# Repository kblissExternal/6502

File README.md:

# 6502
My implementation of Ben Eater's 6502 design (https://eater.net/6502).

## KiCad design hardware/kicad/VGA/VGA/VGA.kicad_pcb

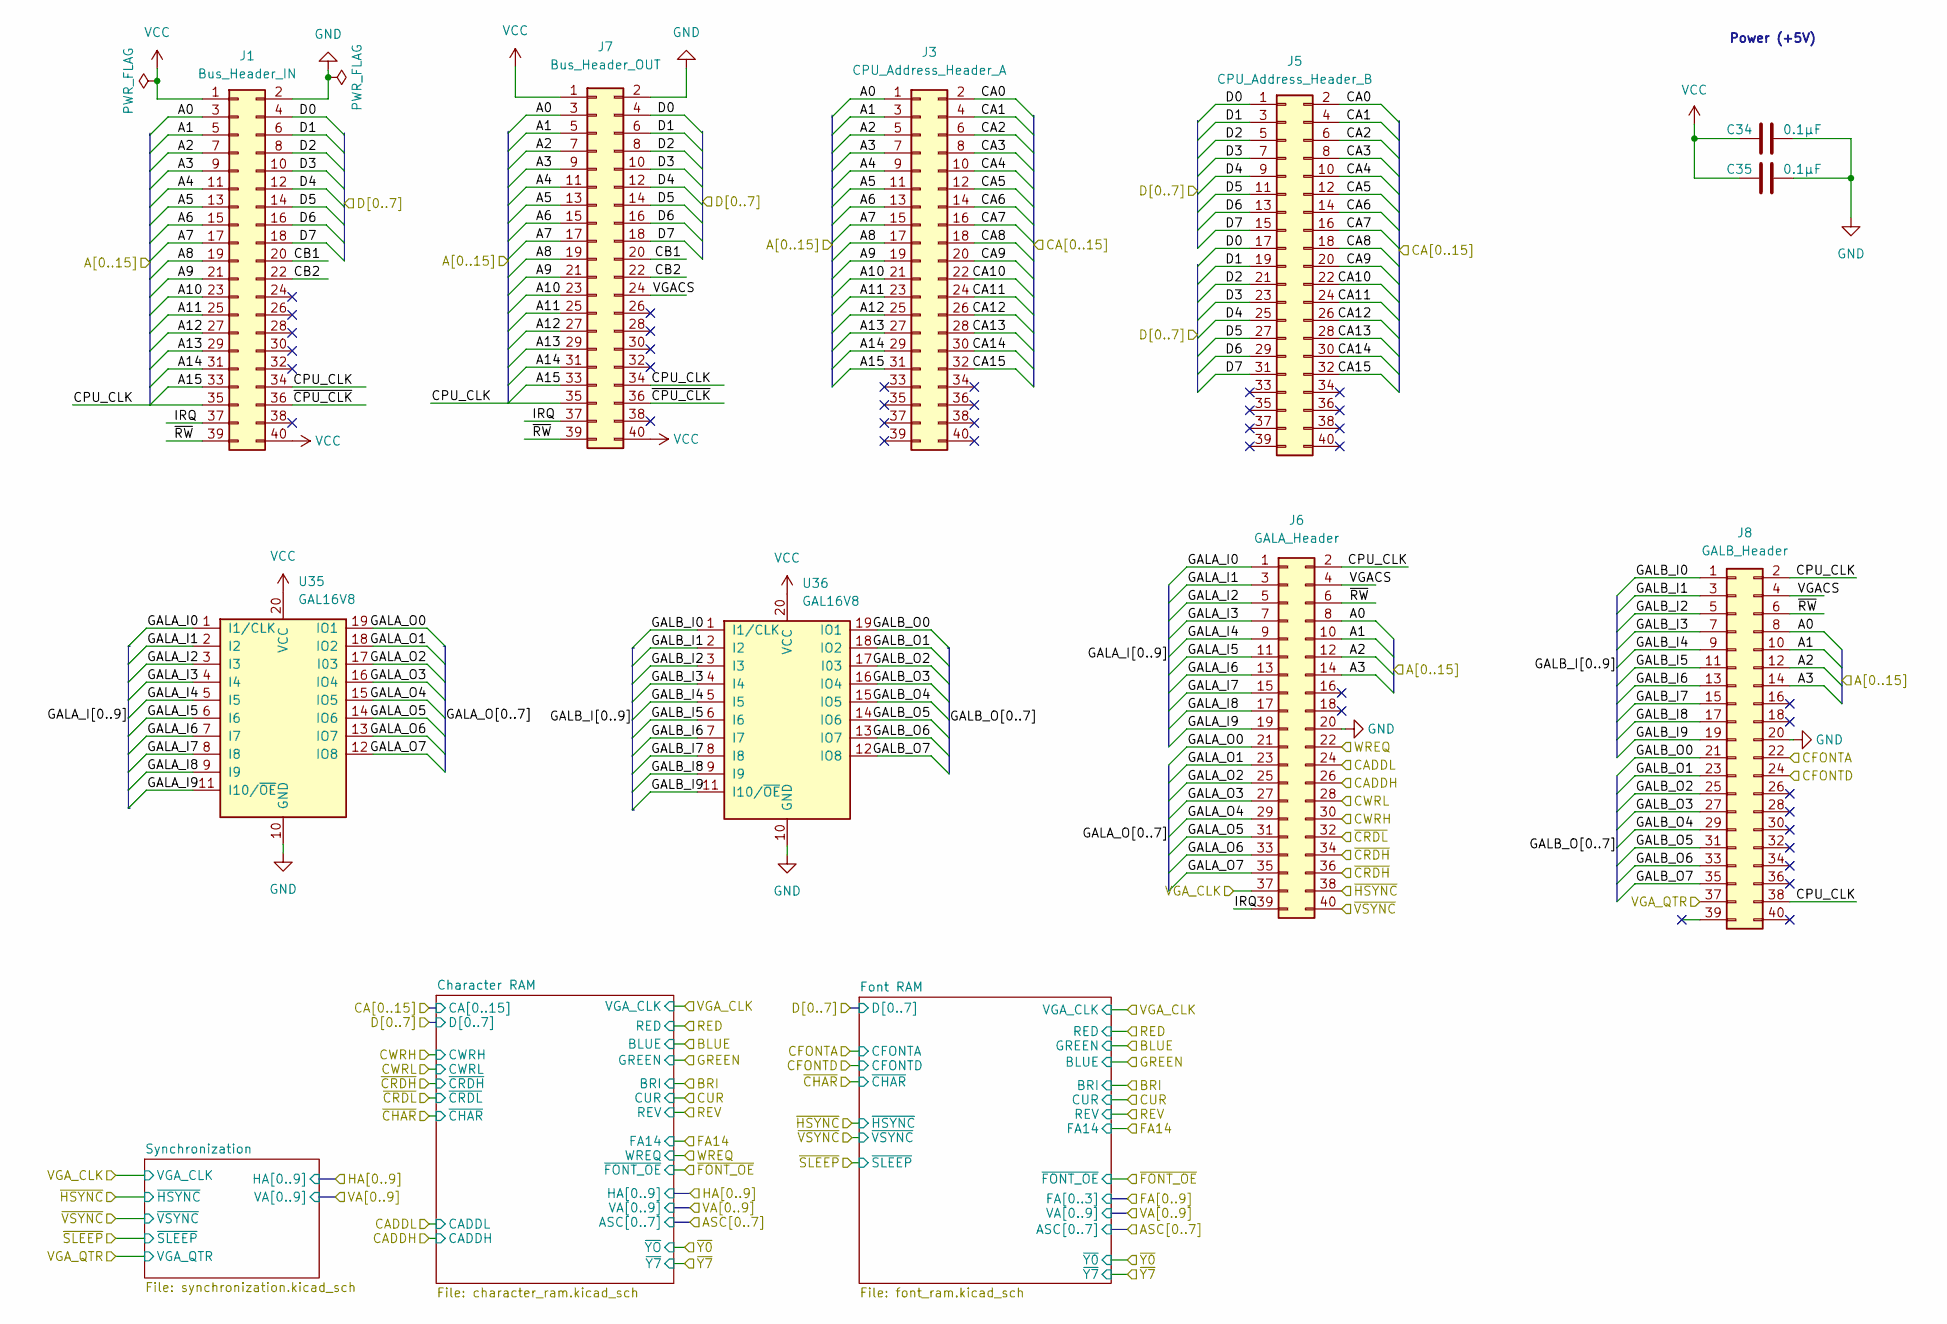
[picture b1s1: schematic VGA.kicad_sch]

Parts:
C34, C35: 0.1µF; C_Disc_D5.0mm_W2.5mm_P2.50mm
J1: Bus_Header_IN; PinHeader_2x20_P2.54mm_Vertical
J3: CPU_Address_Header_A; PinHeader_2x20_P2.54mm_Vertical
J5: CPU_Address_Header_B; PinHeader_2x20_P2.54mm_Vertical
J6: GALA_Header; PinHeader_2x20_P2.54mm_Vertical
J7: Bus_Header_OUT; PinHeader_2x20_P2.54mm_Vertical
J8: GALB_Header; PinHeader_2x20_P2.54mm_Vertical
U35, U36: GAL16V8; DIP-20_W7.62mm_Socket

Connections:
/A0: J1.3, J3.1, J6.8, J7.3, J8.8
/A1: J1.5, J3.3, J6.10, J7.5, J8.10
/A2: J1.7, J3.5, J6.12, J7.7, J8.12
/A3: J1.9, J3.7, J6.14, J7.9, J8.14
/A4: J1.11, J3.9, J7.11
/A5: J1.13, J3.11, J7.13
/A6: J1.15, J3.13, J7.15
/A7: J1.17, J3.15, J7.17
/A8: J1.19, J3.17, J7.19
/A9: J1.21, J3.19, J7.21
/A10: J1.23, J3.21, J7.23
/A11: J1.25, J3.23, J7.25
/A12: J1.27, J3.25, J7.27
/A13: J1.29, J3.27, J7.29
/A14: J1.31, J3.29, J7.31
/A15: J1.33, J3.31, J7.33
/CA0: J3.2, J5.2; also elsewhere on the board
/CA1: J3.4, J5.4; also elsewhere on the board
/CA2: J3.6, J5.6; also elsewhere on the board
/CA3: J3.8, J5.8; also elsewhere on the board
/CA4: J3.10, J5.10; also elsewhere on the board
/CA5: J3.12, J5.12; also elsewhere on the board
/CA6: J3.14, J5.14; also elsewhere on the board
/CA7: J3.16, J5.16; also elsewhere on the board
/CA8: J3.18, J5.18; also elsewhere on the board
/CA9: J3.20, J5.20; also elsewhere on the board
/CA10: J3.22, J5.22; also elsewhere on the board
/CA11: J3.24, J5.24; also elsewhere on the board
/CA12: J3.26, J5.26; also elsewhere on the board
/CA13: J3.28, J5.28; also elsewhere on the board
/CA14: J3.30, J5.30; also elsewhere on the board
/CA15: J3.32, J5.32; also elsewhere on the board
/CADDH: J6.26
/CADDL: J6.24; also elsewhere on the board
/CB1: J1.20, J7.20
/CB2: J1.22, J7.22
/CFONTA: J8.22; also elsewhere on the board
/CPU_CLK: J1.34, J1.35, J6.2, J7.34, J7.35, J8.2, J8.38
/CWRH: J6.30; also elsewhere on the board
/CWRL: J6.28; also elsewhere on the board
/D0: J1.4, J5.1, J5.17, J7.4; also elsewhere on the board
/D1: J1.6, J5.3, J5.19, J7.6; also elsewhere on the board
/D2: J1.8, J5.5, J5.21, J7.8; also elsewhere on the board
/D3: J1.10, J5.7, J5.23, J7.10; also elsewhere on the board
/D4: J1.12, J5.9, J5.25, J7.12; also elsewhere on the board
/D5: J1.14, J5.11, J5.27, J7.14; also elsewhere on the board
/D6: J1.16, J5.13, J5.29, J7.16; also elsewhere on the board
/D7: J1.18, J5.15, J5.31, J7.18; also elsewhere on the board
/GALA_I0: J6.1, U35.1 (I1/CLK)
/GALA_I1: J6.3, U35.2 (I2)
/GALA_I2: J6.5, U35.3 (I3)
/GALA_I3: J6.7, U35.4 (I4)
/GALA_I4: J6.9, U35.5 (I5)
/GALA_I5: J6.11, U35.6 (I6)
/GALA_I6: J6.13, U35.7 (I7)
/GALA_I7: J6.15, U35.8 (I8)
/GALA_I8: J6.17, U35.9 (I9)
/GALA_I9: J6.19, U35.11 (I10/~OE)
/GALA_O0: J6.21, U35.19 (IO1)
/GALA_O1: J6.23, U35.18 (IO2)
/GALA_O2: J6.25, U35.17 (I03)
/GALA_O3: J6.27, U35.16 (IO4)
/GALA_O4: J6.29, U35.15 (IO5)
/GALA_O5: J6.31, U35.14 (IO6)
/GALA_O6: J6.33, U35.13 (IO7)
/GALA_O7: J6.35, U35.12 (IO8)
/GALB_I0: J8.1, U36.1 (I1/CLK)
/GALB_I1: J8.3, U36.2 (I2)
/GALB_I2: J8.5, U36.3 (I3)
/GALB_I3: J8.7, U36.4 (I4)
/GALB_I4: J8.9, U36.5 (I5)
/GALB_I5: J8.11, U36.6 (I6)
/GALB_I6: J8.13, U36.7 (I7)
/GALB_I7: J8.15, U36.8 (I8)
/GALB_I8: J8.17, U36.9 (I9)
/GALB_I9: J8.19, U36.11 (I10/~OE)
/GALB_O0: J8.21, U36.19 (IO1)
/GALB_O1: J8.23, U36.18 (IO2)
/GALB_O2: J8.25, U36.17 (I03)
/GALB_O3: J8.27, U36.16 (IO4)
/GALB_O4: J8.29, U36.15 (IO5)
/GALB_O5: J8.31, U36.14 (IO6)
/GALB_O6: J8.33, U36.13 (IO7)
/GALB_O7: J8.35, U36.12 (IO8)
/IRQ: J1.37, J6.39, J7.37
/VGACS: J6.4, J7.24, J8.4
/VGA_CLK: J6.37; also elsewhere on the board
/VGA_QTR: J8.37; also elsewhere on the board
/WREQ: J6.22; also elsewhere on the board
/~CPU_CLK: J1.36, J7.36
/~CRDH: J6.34, J6.36; also elsewhere on the board
/~CRDL: J6.32; also elsewhere on the board
/~HSYNC: J6.38; also elsewhere on the board
/~RW: J1.39, J6.6, J7.39, J8.6
/~VSYNC: J6.40; also elsewhere on the board

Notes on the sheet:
Power (+5V)

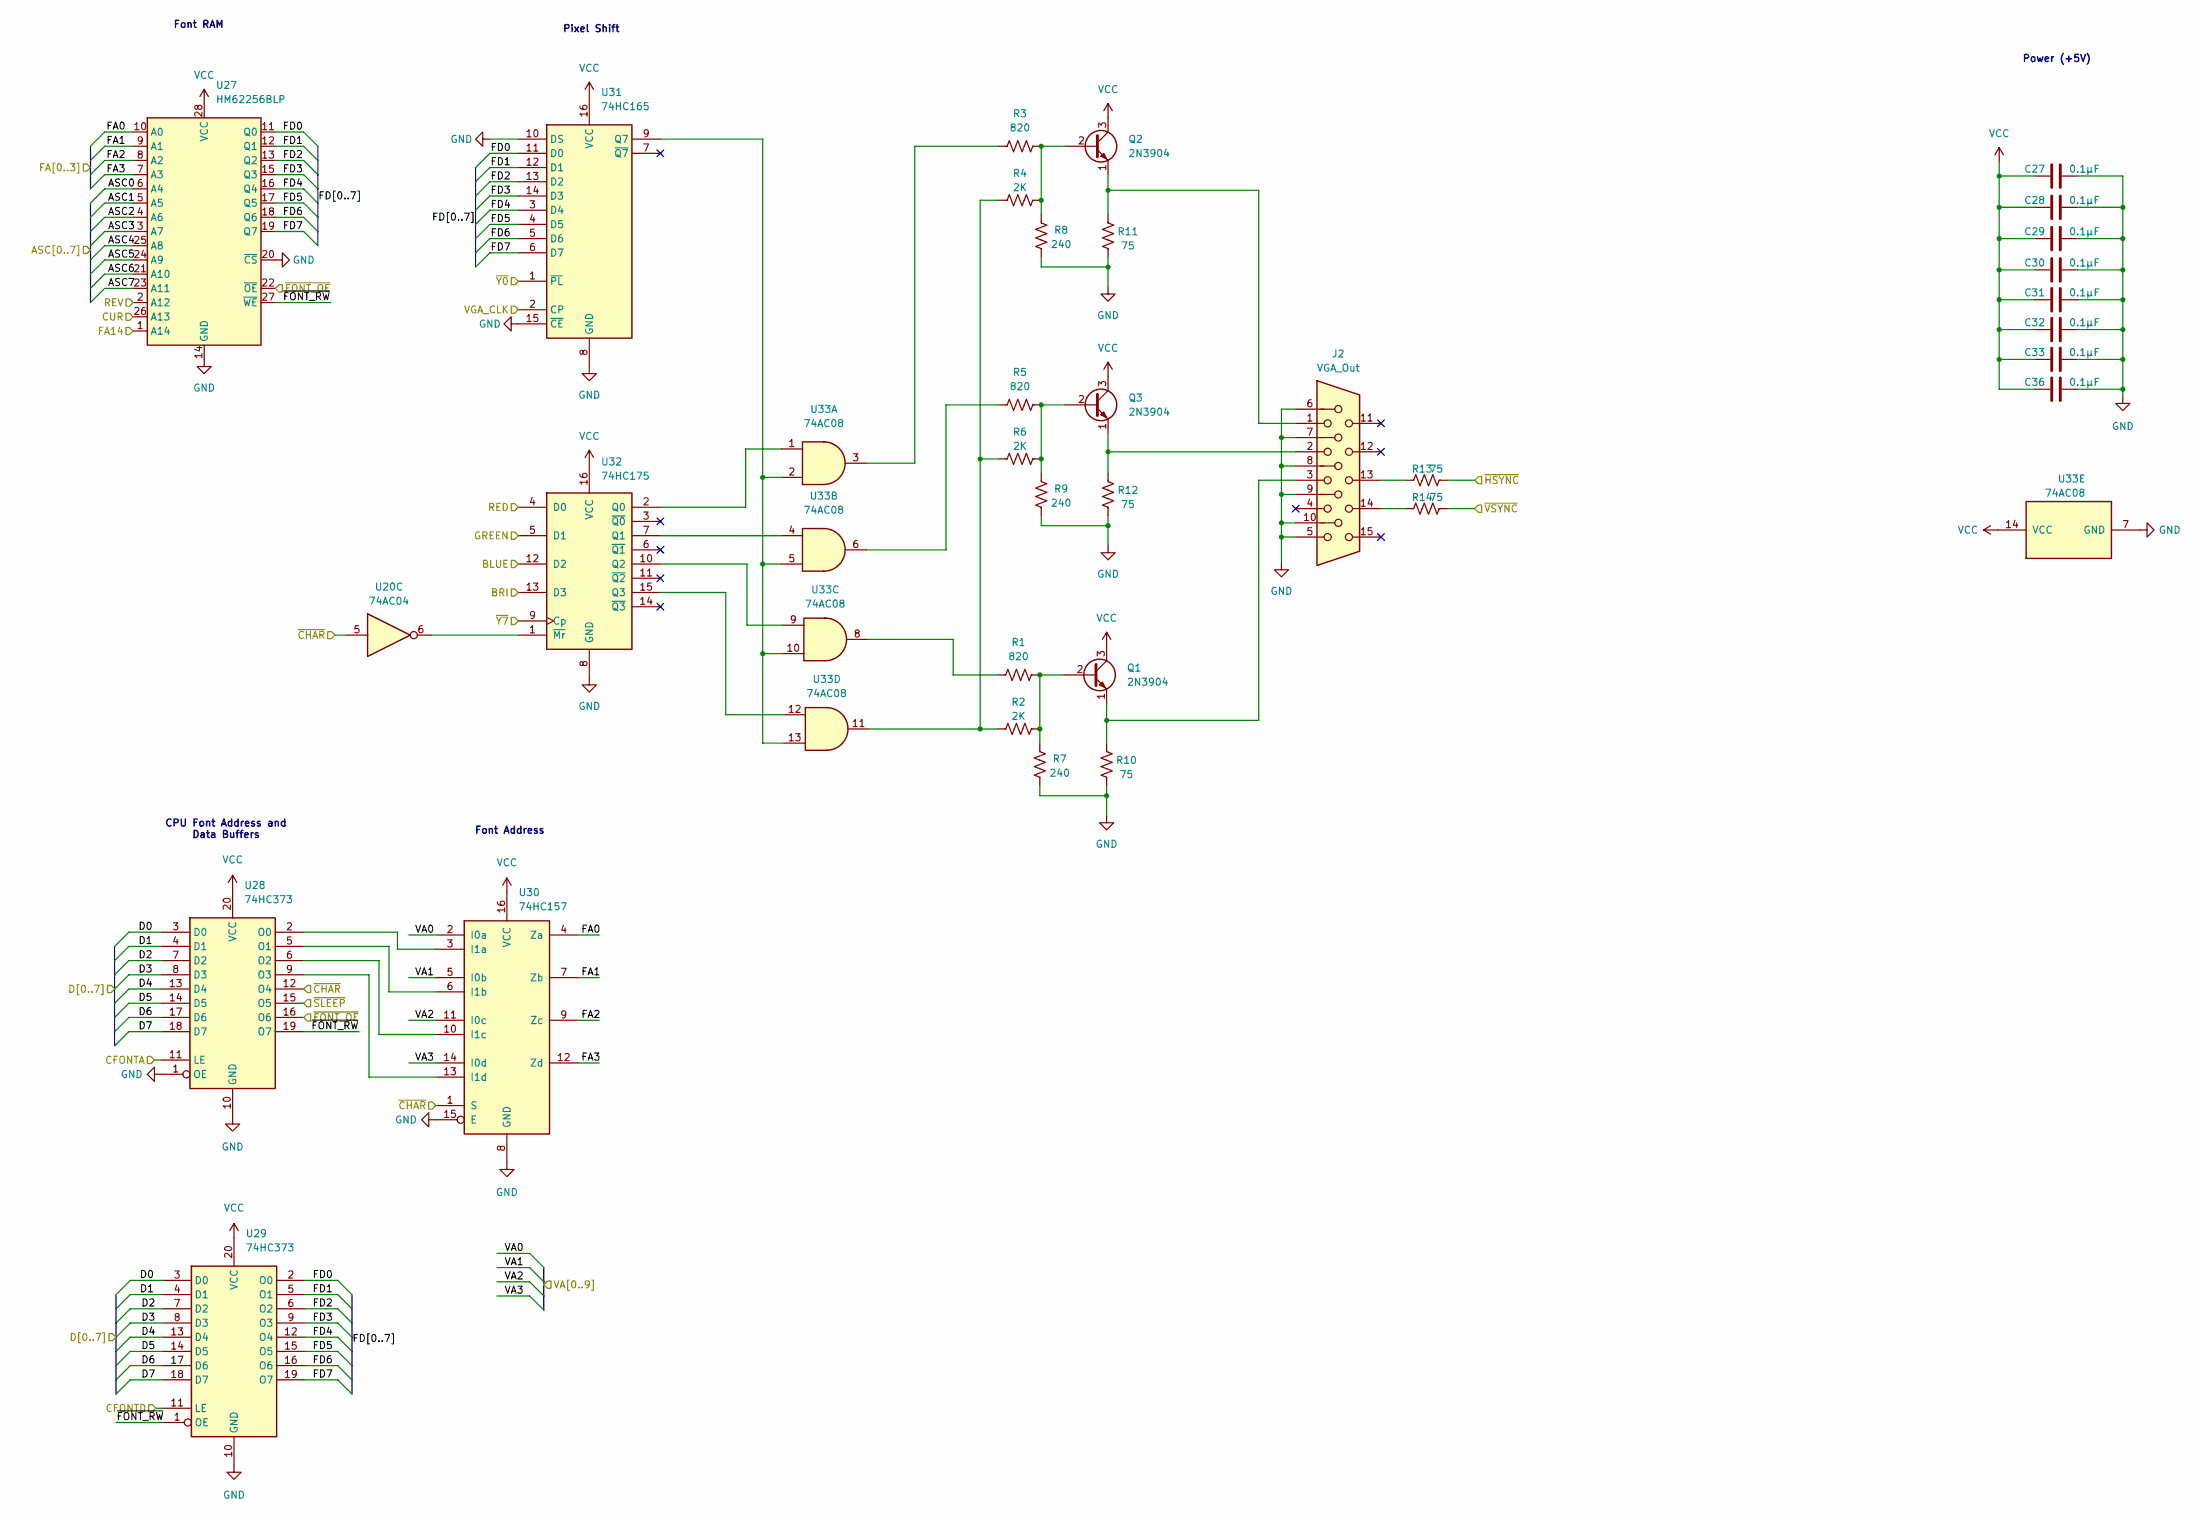
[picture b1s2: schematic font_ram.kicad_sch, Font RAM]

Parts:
C27, C28, C29, C30, C31, C32, C33, C36: 0.1µF; C_Disc_D5.0mm_W2.5mm_P2.50mm
J2: VGA_Out; TE_1-1734530-1
Q1, Q2, Q3: 2N3904; TO-92_Inline
R1, R3, R5: 820; R_Axial_DIN0207_L6.3mm_D2.5mm_P10.16mm_Horizontal
R2, R4, R6: 2K; R_Axial_DIN0207_L6.3mm_D2.5mm_P10.16mm_Horizontal
R7, R8, R9: 240; R_Axial_DIN0207_L6.3mm_D2.5mm_P10.16mm_Horizontal
R10, R11, R12, R13, R14: 75; R_Axial_DIN0207_L6.3mm_D2.5mm_P10.16mm_Horizontal
U20: 74AC04; DIP-14_W7.62mm_Socket
U27: HM62256BLP; DIP-28_W15.24mm_Socket
U28, U29: 74HC373; DIP-20_W7.62mm_Socket
U30: 74HC157; DIP-16_W7.62mm_Socket
U31: 74HC165; DIP-16_W7.62mm_Socket
U32: 74HC175; DIP-16_W7.62mm_Socket
U33: 74AC08; DIP-14_W7.62mm_Socket

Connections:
/ASC0: U27.6 (A4); also elsewhere on the board
/ASC1: U27.5 (A5); also elsewhere on the board
/ASC2: U27.4 (A6); also elsewhere on the board
/ASC3: U27.3 (A7); also elsewhere on the board
/ASC4: U27.25 (A8); also elsewhere on the board
/ASC5: U27.24 (A9); also elsewhere on the board
/ASC6: U27.21 (A10); also elsewhere on the board
/ASC7: U27.23 (A11); also elsewhere on the board
/BLUE: U32.5 (D1); also elsewhere on the board
/BRI: U32.13 (D3); also elsewhere on the board
/CFONTA: U28.11 (LE); also elsewhere on the board
/CUR: U27.26 (A13); also elsewhere on the board
/Character RAM/~Y7: U32.9 (Cp); also elsewhere on the board
/Character RAM/~YO: U31.1 (~PL); also elsewhere on the board
/D0: U28.3 (D0), U29.3 (D0); also elsewhere on the board
/D1: U28.4 (D1), U29.4 (D1); also elsewhere on the board
/D2: U28.7 (D2), U29.7 (D2); also elsewhere on the board
/D3: U28.8 (D3), U29.8 (D3); also elsewhere on the board
/D4: U28.13 (D4), U29.13 (D4); also elsewhere on the board
/D5: U28.14 (D5), U29.14 (D5); also elsewhere on the board
/D6: U28.17 (D6), U29.17 (D6); also elsewhere on the board
/D7: U28.18 (D7), U29.18 (D7); also elsewhere on the board
/FA0: U27.10 (A0), U30.4 (Za)
/FA1: U27.9 (A1), U30.7 (Zb)
/FA2: U27.8 (A2), U30.9 (Zc)
/FA3: U27.7 (A3), U30.12 (Zd)
/FA14: U27.1 (A14); also elsewhere on the board
/Font RAM/FD0: U27.11 (Q0), U29.2 (O0), U31.11 (D0)
/Font RAM/FD1: U27.12 (Q1), U29.5 (O1), U31.12 (D1)
/Font RAM/FD2: U27.13 (Q2), U29.6 (O2), U31.13 (D2)
/Font RAM/FD3: U27.15 (Q3), U29.9 (O3), U31.14 (D3)
/Font RAM/FD4: U27.16 (Q4), U29.12 (O4), U31.3 (D4)
/Font RAM/FD5: U27.17 (Q5), U29.15 (O5), U31.4 (D5)
/Font RAM/FD6: U27.18 (Q6), U29.16 (O6), U31.5 (D6)
/Font RAM/FD7: U27.19 (Q7), U29.19 (O7), U31.6 (D7)
/GREEN: U32.12 (D2); also elsewhere on the board
/RED: U32.4 (D0); also elsewhere on the board
/REV: U27.2 (A12); also elsewhere on the board
/VA0: U30.2 (I0a); also elsewhere on the board
/VA1: U30.5 (I0b); also elsewhere on the board
/VA2: U30.11 (I0c); also elsewhere on the board
/VGA_CLK: U31.2 (CP); also elsewhere on the board
/~CHAR: U20.5, U28.12 (O4), U30.1 (S); also elsewhere on the board
/~FONT_OE: U27.22 (~OE), U28.16 (O6); also elsewhere on the board
/~HSYNC: R13.1; also elsewhere on the board
/~SLEEP: U28.15 (O5); also elsewhere on the board
/~VSYNC: R14.1; also elsewhere on the board
unnamed: J2.1, Q2.1 (E), R11.2
unnamed: J2.2, Q3.1 (E), R12.2
unnamed: J2.3, Q1.1 (E), R10.2
unnamed: J2.13, R13.2
unnamed: J2.14, R14.2
unnamed: Q1.2 (B), R1.2, R2.2, R7.2
unnamed: Q2.2 (B), R3.2, R4.2, R8.2
unnamed: Q3.2 (B), R5.2, R6.2, R9.2
unnamed: R1.1, U33.8
unnamed: R2.1, R4.1, R6.1, U33.11
unnamed: R3.1, U33.3
unnamed: R5.1, U33.6
unnamed: U20.6, U32.1 (~Mr)
unnamed: U28.2 (O0), U30.3 (I1a)
unnamed: U28.5 (O1), U30.6 (I1b)
unnamed: U28.6 (O2), U30.10 (I1c)
unnamed: U31.9 (Q7), U33.2, U33.5, U33.10, U33.13
unnamed: U32.2 (Q0), U33.1
unnamed: U32.7 (Q1), U33.4
unnamed: U32.10 (Q2), U33.9
unnamed: U32.15 (Q3), U33.12

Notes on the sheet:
Pixel Shift
CPU Font Address and Data Buffers
Font Address
Power (+5V)
Font RAM

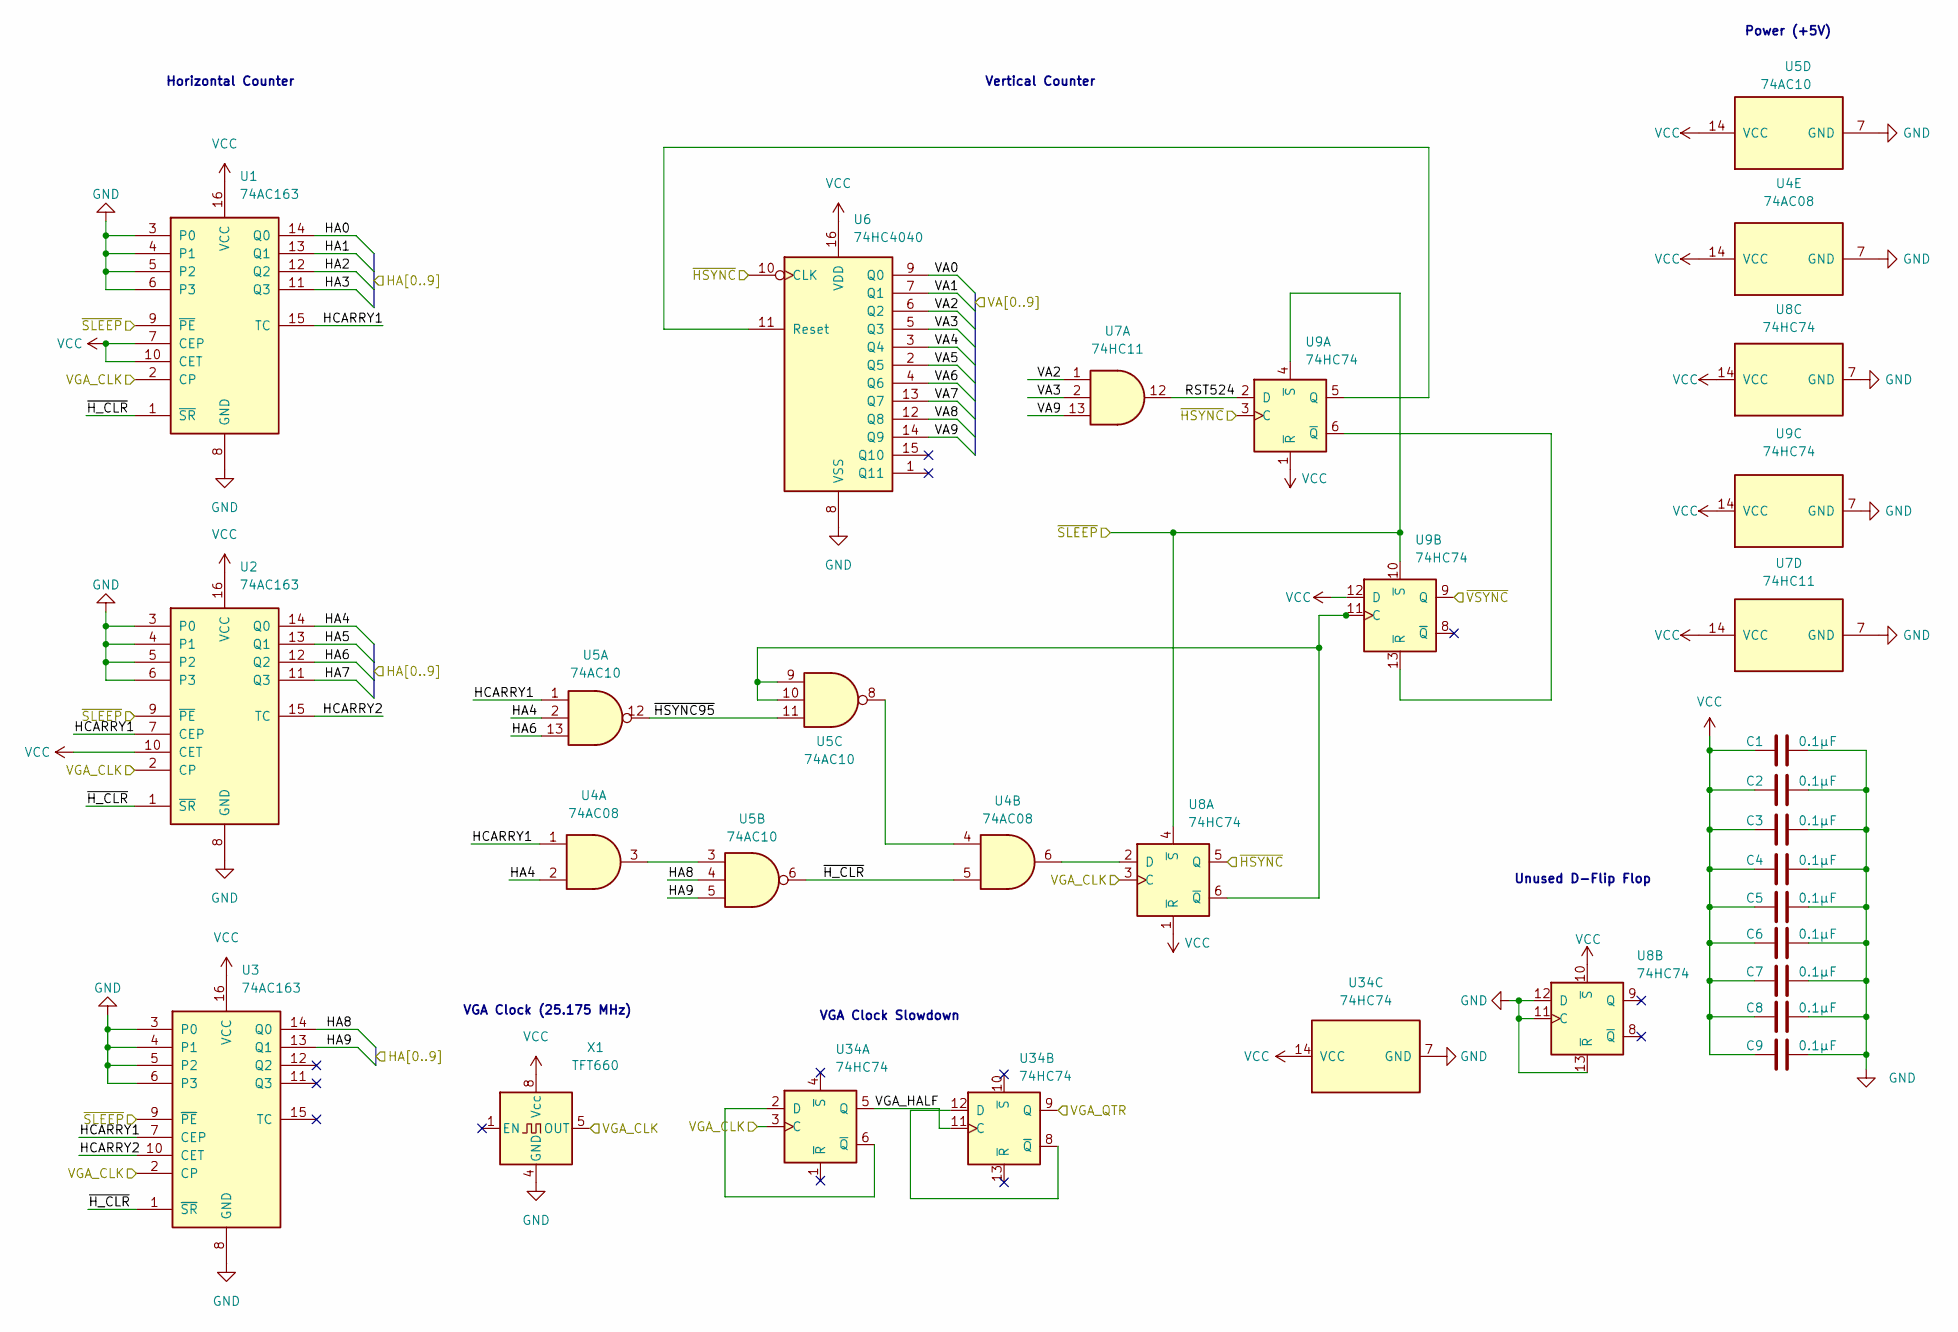
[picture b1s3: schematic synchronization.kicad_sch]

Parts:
C1, C2, C3, C4, C5, C6, C7, C8, C9: 0.1µF; C_Disc_D5.0mm_W2.5mm_P2.50mm
U1, U2, U3: 74AC163; DIP-16_W7.62mm_Socket
U4: 74AC08; DIP-14_W7.62mm_Socket
U5: 74AC10; DIP-14_W7.62mm_Socket
U6: 74HC4040; DIP-16_W7.62mm_Socket
U7: 74HC11; DIP-14_W7.62mm_Socket
U8, U9, U34: 74HC74; DIP-14_W7.62mm_Socket
X1: TFT660; Oscillator_DIP-8

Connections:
/HA0: U1.14 (Q0); also elsewhere on the board
/HA1: U1.13 (Q1); also elsewhere on the board
/HA2: U1.12 (Q2); also elsewhere on the board
/HA3: U1.11 (Q3); also elsewhere on the board
/HA4: U2.14 (Q0), U4.2, U5.2; also elsewhere on the board
/HA5: U2.13 (Q1); also elsewhere on the board
/HA6: U2.12 (Q2), U5.13; also elsewhere on the board
/HA7: U2.11 (Q3); also elsewhere on the board
/HA8: U3.14 (Q0), U5.4; also elsewhere on the board
/HA9: U3.13 (Q1), U5.5; also elsewhere on the board
/Synchronization/HCARRY1: U1.15 (TC), U2.7 (CEP), U3.7 (CEP), U4.1, U5.1
/Synchronization/HCARRY2: U2.15 (TC), U3.10 (CET)
/Synchronization/RST524: U7.12, U9.2 (D)
/Synchronization/VGA_HALF: U34.5 (Q), U34.11 (C)
/Synchronization/~HSYNC95: U5.11, U5.12
/Synchronization/~H_CLR: U1.1 (~SR), U2.1 (~SR), U3.1 (~SR), U4.5, U5.6
/VA0: U6.9 (Q0); also elsewhere on the board
/VA1: U6.7 (Q1); also elsewhere on the board
/VA2: U6.6 (Q2), U7.1; also elsewhere on the board
/VA4: U6.3 (Q4); also elsewhere on the board
/VA5: U6.2 (Q5); also elsewhere on the board
/VA6: U6.4 (Q6); also elsewhere on the board
/VA7: U6.13 (Q7); also elsewhere on the board
/VA8: U6.12 (Q8); also elsewhere on the board
/VA9: U6.14 (Q9), U7.13; also elsewhere on the board
/VGA_CLK: U1.2 (CP), U2.2 (CP), U3.2 (CP), U8.3 (C), U34.3 (C), X1.5 (OUT); also elsewhere on the board
/VGA_QTR: U34.9 (Q); also elsewhere on the board
/~HSYNC: U6.10 (CLK), U8.5 (Q), U9.3 (C); also elsewhere on the board
/~SLEEP: U1.9 (~PE), U2.9 (~PE), U3.9 (~PE), U8.4 (~S), U9.4 (~S), U9.10 (~S); also elsewhere on the board
/~VSYNC: U9.9 (Q); also elsewhere on the board
unnamed: U4.3, U5.3
unnamed: U4.4, U5.8
unnamed: U4.6, U8.2 (D)
unnamed: U5.9, U5.10, U8.6 (~Q), U9.11 (C)
unnamed: U6.11 (Reset), U9.5 (Q)
unnamed: U9.6 (~Q), U9.13 (~R)
unnamed: U34.2 (D), U34.6 (~Q)
unnamed: U34.8 (~Q), U34.12 (D)

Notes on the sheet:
VGA Clock Slowdown
Vertical Counter
Power (+5V)
VGA Clock (25.175 MHz)
Horizontal Counter
Unused D-Flip Flop

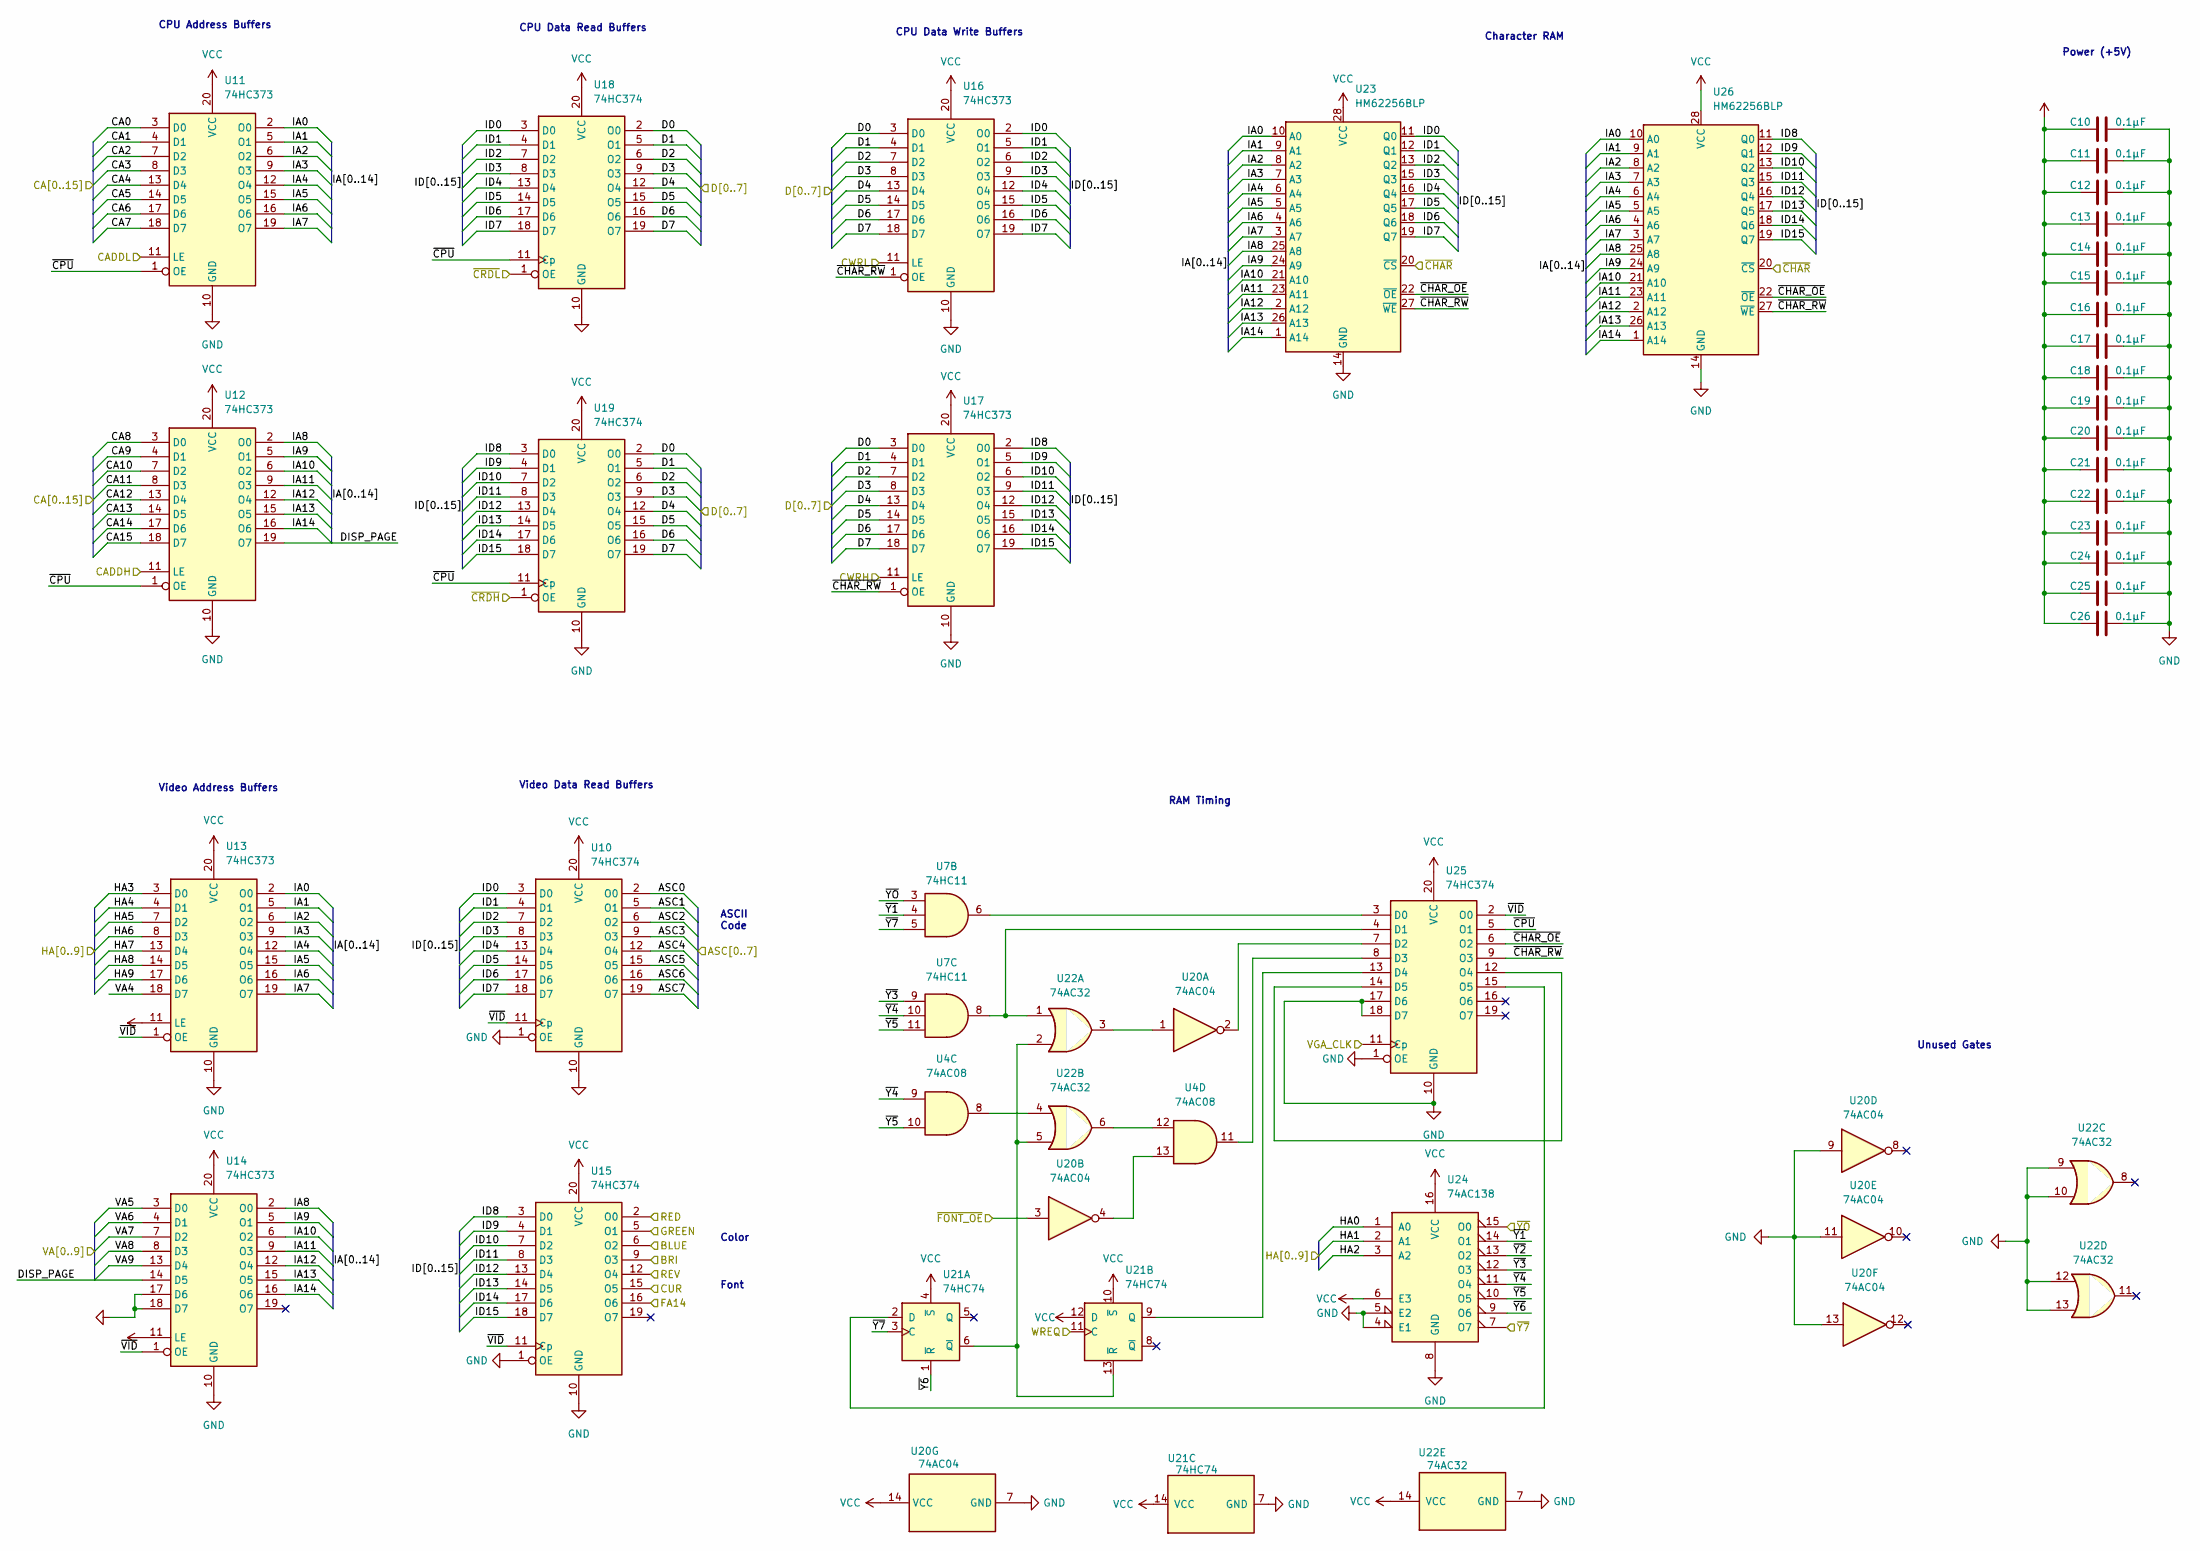
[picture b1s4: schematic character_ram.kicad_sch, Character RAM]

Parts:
C10, C11, C12, C13, C14, C15, C16, C17, C18, C19, C20, C21, C22, C23, C24, C25, C26: 0.1µF; C_Disc_D5.0mm_W2.5mm_P2.50mm
U4: 74AC08; DIP-14_W7.62mm_Socket
U7: 74HC11; DIP-14_W7.62mm_Socket
U10, U15, U18, U19, U25: 74HC374; DIP-20_W7.62mm_Socket
U11, U12, U13, U14, U16, U17: 74HC373; DIP-20_W7.62mm_Socket
U20: 74AC04; DIP-14_W7.62mm_Socket
U21: 74HC74; DIP-14_W7.62mm_Socket
U22: 74AC32; DIP-14_W7.62mm_Socket
U23, U26: HM62256BLP; DIP-28_W15.24mm_Socket
U24: 74AC138; DIP-16_W7.62mm_Socket

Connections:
/ASC0: U10.2 (O0); also elsewhere on the board
/ASC1: U10.5 (O1); also elsewhere on the board
/ASC2: U10.6 (O2); also elsewhere on the board
/ASC3: U10.9 (O3); also elsewhere on the board
/ASC4: U10.12 (O4); also elsewhere on the board
/ASC5: U10.15 (O5); also elsewhere on the board
/ASC6: U10.16 (O6); also elsewhere on the board
/ASC7: U10.19 (O7); also elsewhere on the board
/BLUE: U15.6 (O2); also elsewhere on the board
/BRI: U15.9 (O3); also elsewhere on the board
/CA0: U11.3 (D0); also elsewhere on the board
/CA1: U11.4 (D1); also elsewhere on the board
/CA2: U11.7 (D2); also elsewhere on the board
/CA3: U11.8 (D3); also elsewhere on the board
/CA4: U11.13 (D4); also elsewhere on the board
/CA5: U11.14 (D5); also elsewhere on the board
/CA6: U11.17 (D6); also elsewhere on the board
/CA7: U11.18 (D7); also elsewhere on the board
/CA8: U12.3 (D0); also elsewhere on the board
/CA9: U12.4 (D1); also elsewhere on the board
/CA10: U12.7 (D2); also elsewhere on the board
/CA11: U12.8 (D3); also elsewhere on the board
/CA12: U12.13 (D4); also elsewhere on the board
/CA13: U12.14 (D5); also elsewhere on the board
/CA14: U12.17 (D6); also elsewhere on the board
/CA15: U12.18 (D7); also elsewhere on the board
/CADDL: U11.11 (LE), U12.11 (LE); also elsewhere on the board
/CUR: U15.15 (O5); also elsewhere on the board
/CWRH: U17.11 (LE); also elsewhere on the board
/CWRL: U16.11 (LE); also elsewhere on the board
/Character RAM/DISP_PAGE: U12.19 (O7), U14.14 (D5)
/Character RAM/IA0: U11.2 (O0), U13.2 (O0), U23.10 (A0), U26.10 (A0)
/Character RAM/IA1: U11.5 (O1), U13.5 (O1), U23.9 (A1), U26.9 (A1)
/Character RAM/IA2: U11.6 (O2), U13.6 (O2), U23.8 (A2), U26.8 (A2)
/Character RAM/IA3: U11.9 (O3), U13.9 (O3), U23.7 (A3), U26.7 (A3)
/Character RAM/IA4: U11.12 (O4), U13.12 (O4), U23.6 (A4), U26.6 (A4)
/Character RAM/IA5: U11.15 (O5), U13.15 (O5), U23.5 (A5), U26.5 (A5)
/Character RAM/IA6: U11.16 (O6), U13.16 (O6), U23.4 (A6), U26.4 (A6)
/Character RAM/IA7: U11.19 (O7), U13.19 (O7), U23.3 (A7), U26.3 (A7)
/Character RAM/IA8: U12.2 (O0), U14.2 (O0), U23.25 (A8), U26.25 (A8)
/Character RAM/IA9: U12.5 (O1), U14.5 (O1), U23.24 (A9), U26.24 (A9)
/Character RAM/IA10: U12.6 (O2), U14.6 (O2), U23.21 (A10), U26.21 (A10)
/Character RAM/IA11: U12.9 (O3), U14.9 (O3), U23.23 (A11), U26.23 (A11)
/Character RAM/IA12: U12.12 (O4), U14.12 (O4), U23.2 (A12), U26.2 (A12)
/Character RAM/IA13: U12.15 (O5), U14.15 (O5), U23.26 (A13), U26.26 (A13)
/Character RAM/IA14: U12.16 (O6), U14.16 (O6), U23.1 (A14), U26.1 (A14)
/Character RAM/ID0: U10.3 (D0), U16.2 (O0), U18.3 (D0), U23.11 (Q0)
/Character RAM/ID1: U10.4 (D1), U16.5 (O1), U18.4 (D1), U23.12 (Q1)
/Character RAM/ID2: U10.7 (D2), U16.6 (O2), U18.7 (D2), U23.13 (Q2)
/Character RAM/ID3: U10.8 (D3), U16.9 (O3), U18.8 (D3), U23.15 (Q3)
/Character RAM/ID4: U10.13 (D4), U16.12 (O4), U18.13 (D4), U23.16 (Q4)
/Character RAM/ID5: U10.14 (D5), U16.15 (O5), U18.14 (D5), U23.17 (Q5)
/Character RAM/ID6: U10.17 (D6), U16.16 (O6), U18.17 (D6), U23.18 (Q6)
/Character RAM/ID7: U10.18 (D7), U16.19 (O7), U18.18 (D7), U23.19 (Q7)
/Character RAM/ID8: U15.3 (D0), U17.2 (O0), U19.3 (D0), U26.11 (Q0)
/Character RAM/ID9: U15.4 (D1), U17.5 (O1), U19.4 (D1), U26.12 (Q1)
/Character RAM/ID10: U15.7 (D2), U17.6 (O2), U19.7 (D2), U26.13 (Q2)
/Character RAM/ID11: U15.8 (D3), U17.9 (O3), U19.8 (D3), U26.15 (Q3)
/Character RAM/ID12: U15.13 (D4), U17.12 (O4), U19.13 (D4), U26.16 (Q4)
/Character RAM/ID13: U15.14 (D5), U17.15 (O5), U19.14 (D5), U26.17 (Q5)
/Character RAM/ID14: U15.17 (D6), U17.16 (O6), U19.17 (D6), U26.18 (Q6)
/Character RAM/ID15: U15.18 (D7), U17.19 (O7), U19.18 (D7), U26.19 (Q7)
/Character RAM/~CHAR_OE: U23.22 (~OE), U25.6 (O2), U26.22 (~OE)
/Character RAM/~CHAR_RW: U16.1 (OE), U17.1 (OE), U23.27 (~WE), U25.9 (O3), U26.27 (~WE)
/Character RAM/~CPU: U11.1 (OE), U12.1 (OE), U18.11 (Cp), U19.11 (Cp), U25.5 (O1)
/Character RAM/~VID: U10.11 (Cp), U13.1 (OE), U14.1 (OE), U15.11 (Cp), U25.2 (O0)
/Character RAM/~Y1: U7.4, U24.14 (O1)
/Character RAM/~Y2: U24.13 (O2)
/Character RAM/~Y3: U7.9, U24.12 (O3)
/Character RAM/~Y4: U4.9, U7.10, U24.11 (O4)
/Character RAM/~Y5: U4.10, U7.11, U24.10 (O5)
/Character RAM/~Y6: U21.1 (~R), U24.9 (O6)
/Character RAM/~Y7: U7.5, U21.3 (C), U24.7 (O7); also elsewhere on the board
/Character RAM/~YO: U7.3, U24.15 (O0); also elsewhere on the board
/D0: U16.3 (D0), U17.3 (D0), U18.2 (O0), U19.2 (O0); also elsewhere on the board
/D1: U16.4 (D1), U17.4 (D1), U18.5 (O1), U19.5 (O1); also elsewhere on the board
/D2: U16.7 (D2), U17.7 (D2), U18.6 (O2), U19.6 (O2); also elsewhere on the board
/D3: U16.8 (D3), U17.8 (D3), U18.9 (O3), U19.9 (O3); also elsewhere on the board
/D4: U16.13 (D4), U17.13 (D4), U18.12 (O4), U19.12 (O4); also elsewhere on the board
/D5: U16.14 (D5), U17.14 (D5), U18.15 (O5), U19.15 (O5); also elsewhere on the board
/D6: U16.17 (D6), U17.17 (D6), U18.16 (O6), U19.16 (O6); also elsewhere on the board
/D7: U16.18 (D7), U17.18 (D7), U18.19 (O7), U19.19 (O7); also elsewhere on the board
/FA14: U15.16 (O6); also elsewhere on the board
/GREEN: U15.5 (O1); also elsewhere on the board
/HA0: U24.1 (A0); also elsewhere on the board
/HA1: U24.2 (A1); also elsewhere on the board
/HA2: U24.3 (A2); also elsewhere on the board
/HA3: U13.3 (D0); also elsewhere on the board
/HA4: U13.4 (D1); also elsewhere on the board
/HA5: U13.7 (D2); also elsewhere on the board
/HA6: U13.8 (D3); also elsewhere on the board
/HA7: U13.13 (D4); also elsewhere on the board
/HA8: U13.14 (D5); also elsewhere on the board
/HA9: U13.17 (D6); also elsewhere on the board
/RED: U15.2 (O0); also elsewhere on the board
/REV: U15.12 (O4); also elsewhere on the board
/VA4: U13.18 (D7); also elsewhere on the board
/VA5: U14.3 (D0); also elsewhere on the board
/VA6: U14.4 (D1); also elsewhere on the board
/VA7: U14.7 (D2); also elsewhere on the board
/VA8: U14.8 (D3); also elsewhere on the board
/VA9: U14.13 (D4); also elsewhere on the board
/VGA_CLK: U25.11 (Cp); also elsewhere on the board
/WREQ: U21.11 (C); also elsewhere on the board
/~CHAR: U23.20 (~CS), U26.20 (~CS); also elsewhere on the board
/~CRDH: U19.1 (OE); also elsewhere on the board
/~CRDL: U18.1 (OE); also elsewhere on the board
/~FONT_OE: U20.3; also elsewhere on the board
unnamed: U20.1, U22.3
unnamed: U20.2, U25.7 (D2)
unnamed: U4.13, U20.4
unnamed: U21.2 (D), U25.15 (O5)
unnamed: U21.9 (Q), U25.13 (D4)
unnamed: U21.6 (~Q), U21.13 (~R), U22.2, U22.5
unnamed: U7.8, U22.1, U25.4 (D1)
unnamed: U4.8, U22.4
unnamed: U4.12, U22.6
unnamed: U7.6, U25.3 (D0)
unnamed: U4.11, U25.8 (D3)
unnamed: U25.12 (O4), U25.14 (D5)

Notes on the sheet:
Unused Gates
CPU Address Buffers
Character RAM
Video Data Read Buffers
Font
RAM Timing
ASCII Code
Power (+5V)
CPU Data Write Buffers
Color
CPU Data Read Buffers
Video Address Buffers

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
